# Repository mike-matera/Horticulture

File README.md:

Horticulture
============

Source and documentation for my project working with the Horticulture department at Cabrillo.

Autonomous Light Sensor (c) by Michael Matera

The Autonomous Light Sensor is licensed under a
Creative Commons Attribution-ShareAlike 4.0 International License.

You should have received a copy of the license along with this
work. If not, see <http://creativecommons.org/licenses/by-sa/4.0/>. 

Attributions

The PCB contains footprints from the SparkFun Eagle library. 
  https://github.com/sparkfun/SparkFun-Eagle-Libraries

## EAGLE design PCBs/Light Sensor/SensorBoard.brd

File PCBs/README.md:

This directory contains the Eagle shematic and PCB files. 

The bill of materials for the PCB can be found here: 
https://docs.google.com/spreadsheets/d/1OfI_GfA84AMtYy2GsPmqO_wkKgt9htvCScB73qxKzeg/edit?usp=sharing

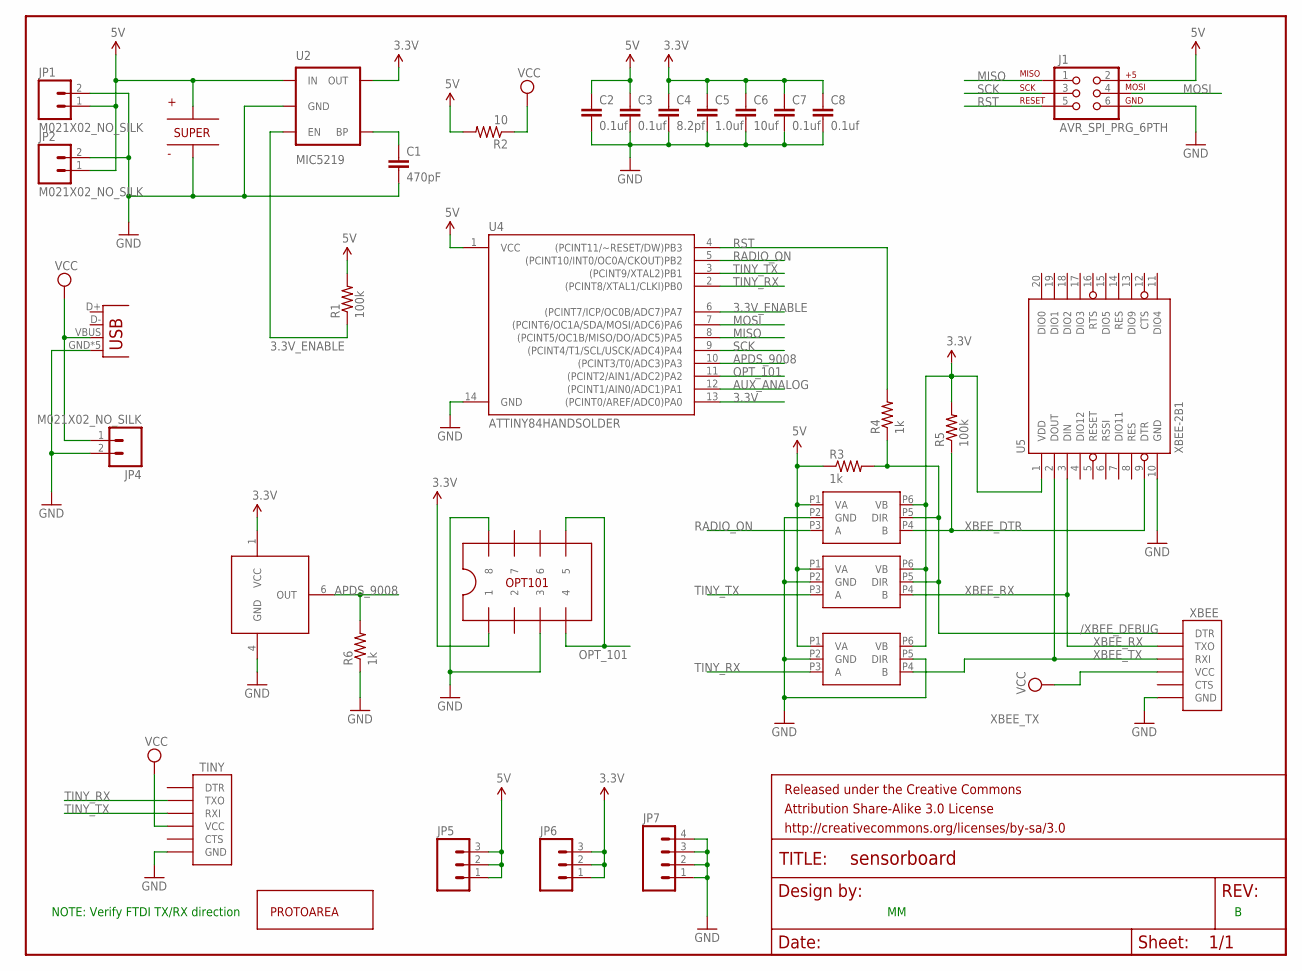
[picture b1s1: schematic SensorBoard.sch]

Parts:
C1: 470pF; 1210
C2, C3, C7, C8: 0.1uf; 1210
C4: 8.2pf; 1210
C5: 1.0uf; 1210
C6: 10uf; 1210
FRAME1: FRAME-LETTER; CREATIVE_COMMONS
J1: AVR_SPI_PRG_6PTH; 2X3
JP1, JP2, JP4: M021X02_NO_SILK; 1X02_NO_SILK
JP3: USBSMD; USB-MINIB
JP5, JP6: M031X03_NO_SILK; 1X03_NO_SILK
JP7: M041X04_NO_SILK; 1X04_NO_SILK
R1, R5: 100k; R1210
R2: 10; AXIAL-0.3
R3, R4, R6: 1k; R1210
TINY: FTDI_DEVICE; FTDI_DEVICE_SIDE
U1: APDS-9008
U2: MIC5219; SOT23-5
U3: OPT101TH; DIL08
U4: ATTINY84HANDSOLDER; SO14-EZ
U5: XBEE-2B1; XBEE-1
U$1: FYD0H225ZF; SUPERCAP-28.5
U$2: PROTOAREA-10X10
U$3, U$4, U$5: SN74LVC1T45; DBV-R-PDSO-G6
XBEE: FTDI_DEVICE; FTDI_DEVICE_SIDE

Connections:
3.3V: C4.1, C5.1, C6.1, C7.1, C8.1, JP6.1, JP6.2, JP6.3, R5.2, U1.1 (VCC), U2.5 (OUT), U3.1, U4.13 ((PCINT0/AREF/ADC0)PA0), U5.1 (VDD), U$3.P6 (VB), U$4.P6 (VB), U$5.P6 (VB)
3.3V_ENABLE: R1.1, U2.3 (EN), U4.6 ((PCINT7/ICP/OC0B/ADC7)PA7)
5V: C2.1, C3.1, J1.2, JP1.1, JP2.1, JP5.1, JP5.2, JP5.3, R1.2, R2.P$2 (2), R3.1, U2.1 (IN), U4.1 (VCC), U$1.+, U$3.P1 (VA), U$4.P1 (VA), U$5.P1 (VA)
/XBEE_DEBUG: R3.2, R4.1, U$3.P5 (DIR), U$4.P5 (DIR), XBEE.P$1 (DTR)
APDS_9008: R6.2, U1.6 (OUT), U4.10 ((PCINT3/T0/ADC3)PA3)
AUX_ANALOG: U4.12 ((PCINT1/AIN0/ADC1)PA1)
GND: C1.2, C2.2, C3.2, C4.2, C5.2, C6.2, C7.2, C8.2, J1.6, JP1.2, JP2.2, JP3.GND, JP3.MTN1 (GND), JP3.MTN2 (GND), JP3.MTN3 (GND), JP3.MTN4 (GND), JP4.2, JP7.1, JP7.2, JP7.3, JP7.4, R6.1, TINY.P$6 (GND), U1.4 (GND), U2.2 (GND), U3.3, U3.8, U4.14 (GND), U5.10 (GND), U$1.-, U$3.P2 (GND), U$4.P2 (GND), U$5.P2 (GND), U$5.P5 (DIR), XBEE.P$6 (GND)
MISO: J1.1, U4.8 ((PCINT5/OC1B/MISO/DO/ADC5)PA5)
MOSI: J1.4, U4.7 ((PCINT6/OC1A/SDA/MOSI/ADC6)PA6)
unnamed: C1.1, U2.4 (BP)
OPT_101: U3.4, U3.5, U4.11 ((PCINT2/AIN1/ADC2)PA2)
RADIO_ON: U4.5 ((PCINT10/INT0/OC0A/CKOUT)PB2), U$3.P3 (A)
RST: J1.5, R4.2, U4.4 ((PCINT11/~RESET/DW)PB3)
SCK: J1.3, U4.9 ((PCINT4/T1/SCL/USCK/ADC4)PA4)
TINY_RX: TINY.P$2 (TXO), U4.2 ((PCINT8/XTAL1/CLKI)PB0), U$5.P3 (A)
TINY_TX: TINY.P$3 (RXI), U4.3 ((PCINT9/XTAL2)PB1), U$4.P3 (A)
VCC: JP3.VBUS, JP4.1, R2.P$1 (1), TINY.P$4 (VCC), XBEE.P$4 (VCC)
XBEE_DTR: R5.1, U5.9 (DTR), U$3.P4 (B)
XBEE_RX: U5.3 (DIN), U$4.P4 (B), XBEE.P$2 (TXO)
XBEE_TX: U5.2 (DOUT), U$5.P4 (B), XBEE.P$3 (RXI)

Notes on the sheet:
NOTE: Verify FTDI TX/RX direction

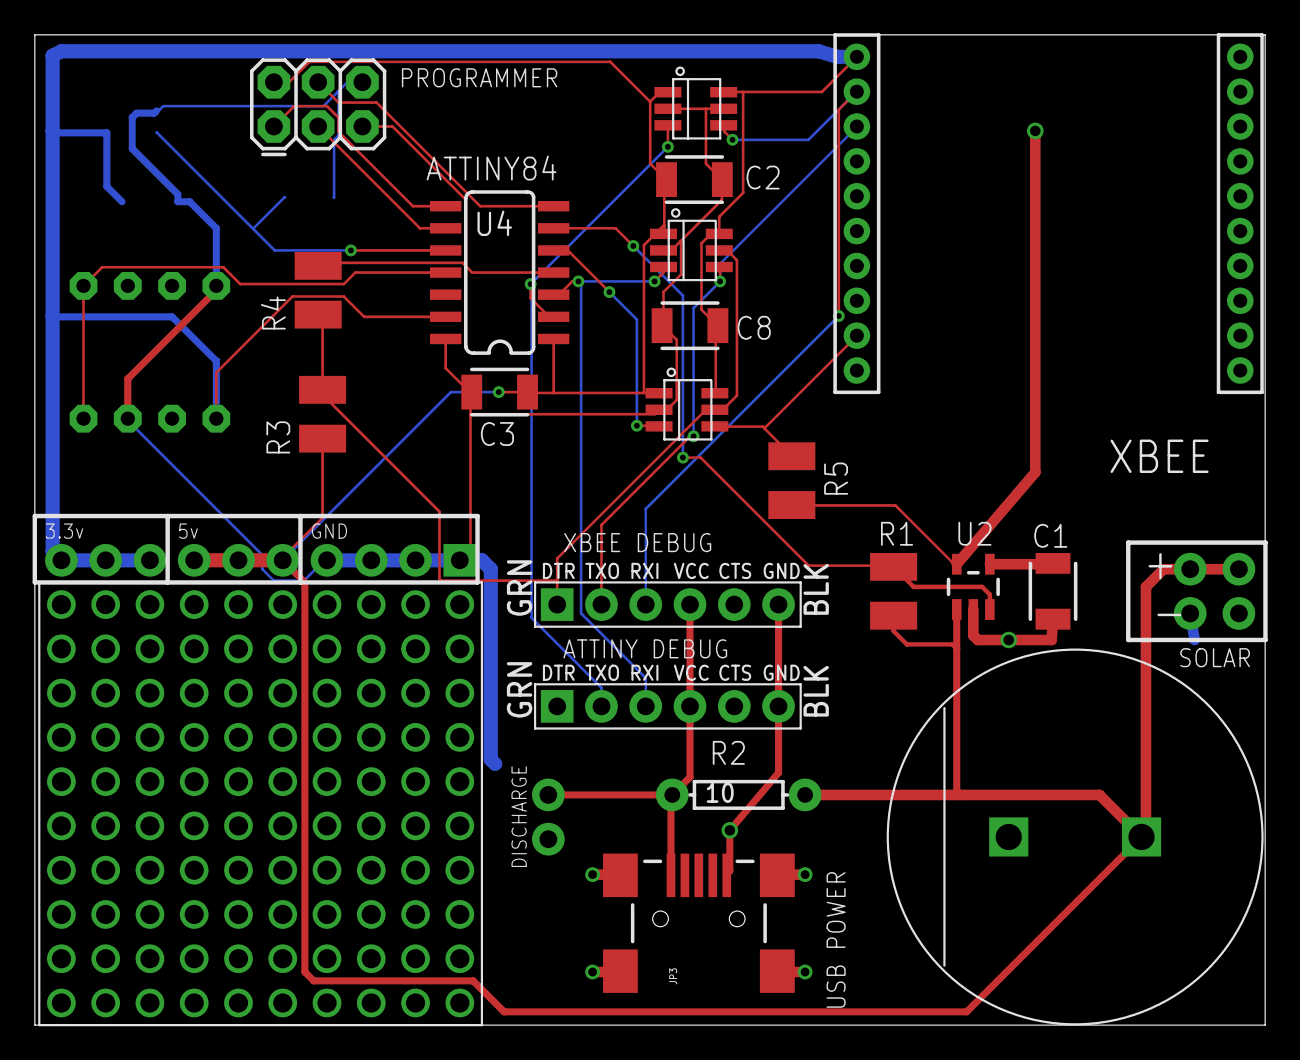
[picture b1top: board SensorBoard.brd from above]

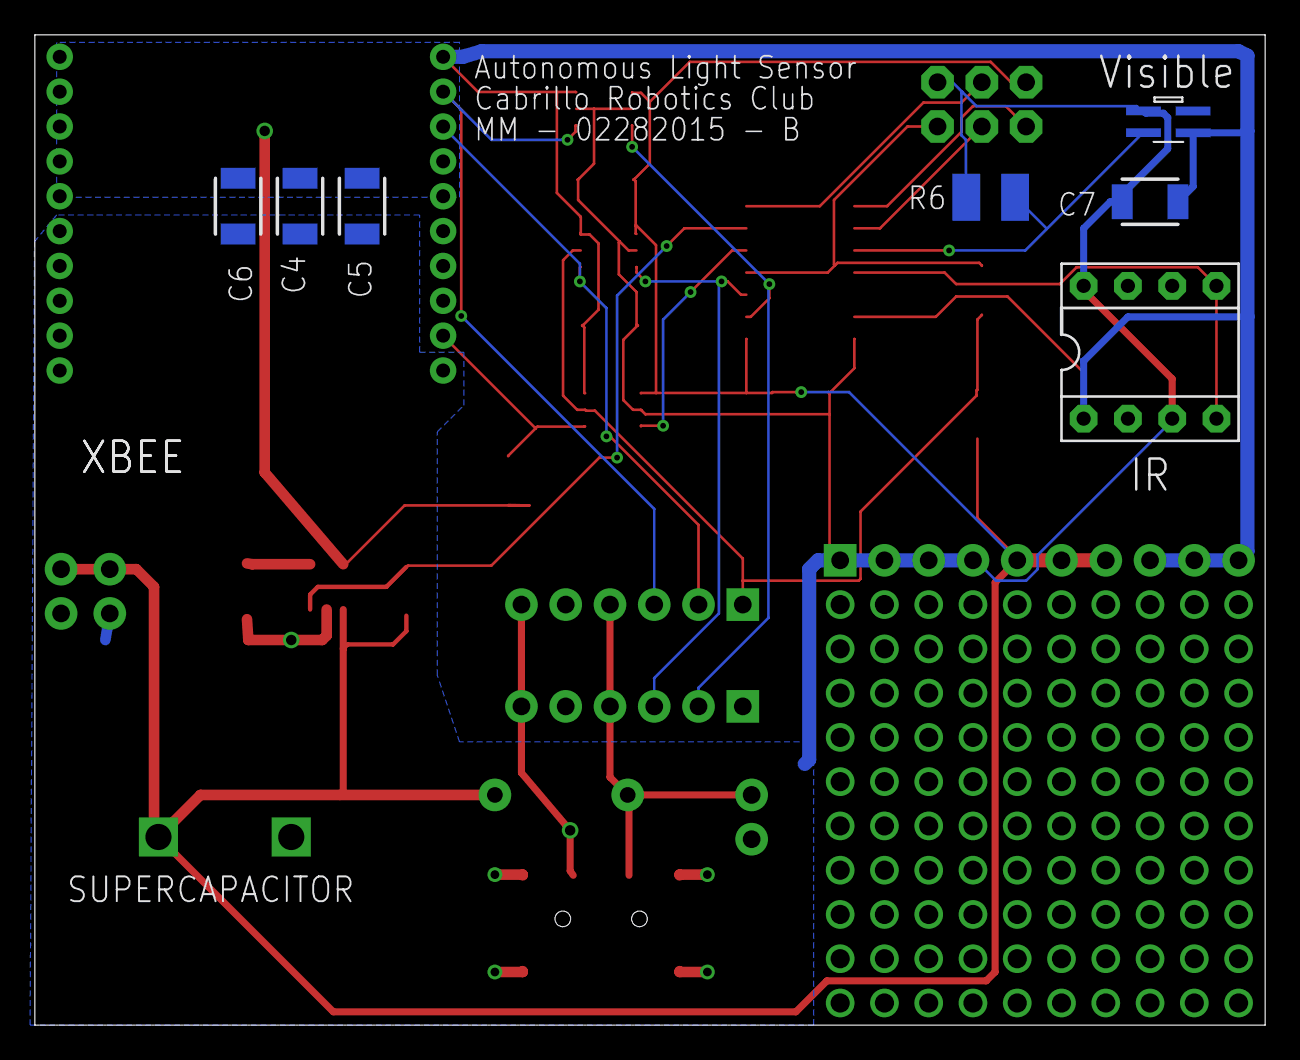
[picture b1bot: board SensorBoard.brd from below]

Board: 2 copper layers, 70.6 x 56.8 mm, 35 parts (7 on the bottom side), 19 nets.

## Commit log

2014-09-23 Initial version of the light sensor
2014-10-03 Changed to using breadboard friendly symbols
2014-10-03 Good to have a picture.
2014-12-01 Added level translator, jumpers
2014-12-07 Cleanups
2014-12-08 Added protection, pinswap level shift, proto area
2014-12-08 Early Board
2014-12-10 Added caps, back to DIPs on everything, fixups, screw holes
2014-12-10 Working layout
2014-12-14 Unrouted
2014-12-20 Version taped out for rev A
2014-12-20 Updated PDF
2015-02-17 Fixes: - Changed to ATTiny84 for more pins - Changed to enable/disable 3.3v LDO to avoid droop conditions
2015-02-17 Initial relayout for the new components
2015-02-21 Working on updates
2015-02-23 Incremental updates
2015-02-23 Simple volgtage reader program
2015-02-24 Still routing and placing
2015-02-27 Almost finished with layout
2015-02-28 Rev. B layout complete, design review soon
2015-02-28 Correct orientation for PDF
2015-03-01 Changed license to CC BY-SA
2015-03-01 Updated to CC 4.0
    I used the wrong plaintext before
2015-03-01 Added license and attribution footer.
2015-03-01 Grounded USB shield
2015-03-09 Changed pullups to 100K to save power
2015-04-21 Mostly working with powerdown

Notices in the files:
parts and their libraries:
MyLibrary: Released under the Creative Commons Attribution Share-Alike 3.0 License
MyLibrary: http://creativecommons.org/licenses/by-sa/3.0
SparkFun-PowerIC: Licensing: CC v3.0 Share-Alike You are welcome to use this library for commercial purposes.
MyLibrary: Released under the Creative Commons
